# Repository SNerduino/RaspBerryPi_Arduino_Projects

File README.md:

# RaspBerryPi_Arduino_Projects
These are my personal tutorials and projects for raspberry pi and (or) arduino.

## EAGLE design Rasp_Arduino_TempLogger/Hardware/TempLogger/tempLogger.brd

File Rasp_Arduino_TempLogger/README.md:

# Temperature plotterThis  project uses a raspberry pi and one or manu arduinos.Each arduino card is connected to a NRF24L01+ RF module that is used for bluetooth low energy communication tool.It also has a humidity-temperature sensor DHT11The raspberry logs the received data and shows it as a graph.For future releases, the raspberry logs are going to be stored in a MySQL database thet can be accessed through A Web app.## Arduino appThe arduino application dépends on the following libraries :DHT Library for communicating with the DHT11 sensorBTLE Library for using NRF24L01+ as A Bluetooth Low Energy advertiserRF24 Library needed for BTLE Library

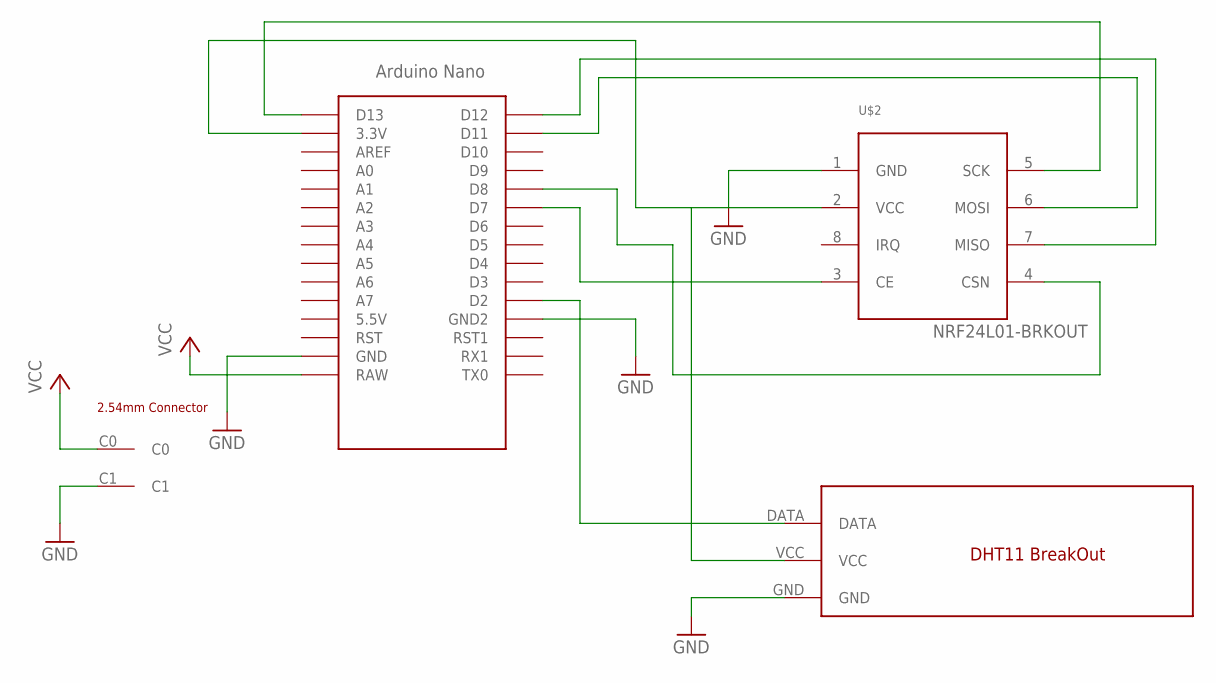
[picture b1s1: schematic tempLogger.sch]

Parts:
U$1: NANO
U$2: NRF24L01-BRKOUT; NRF24L01-BKKOUT
U$3: DHT11BREAKOUTVERTICAL; DHT11BREAKOUT_VERTICAL
U$4: TWO_PINS_CONNECTOR_2_54MM

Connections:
GND: U$1.GND, U$1.GND1 (GND2), U$2.1 (GND), U$3.GND, U$4.C1
unnamed: U$1.3.3V, U$2.2 (VCC), U$3.VCC
unnamed: U$1.D13, U$2.5 (SCK)
unnamed: U$1.D12, U$2.7 (MISO)
unnamed: U$1.D11, U$2.6 (MOSI)
unnamed: U$1.D7, U$2.3 (CE)
unnamed: U$1.D8, U$2.4 (CSN)
unnamed: U$1.D2, U$3.DATA
VCC: U$1.RAW, U$4.C0

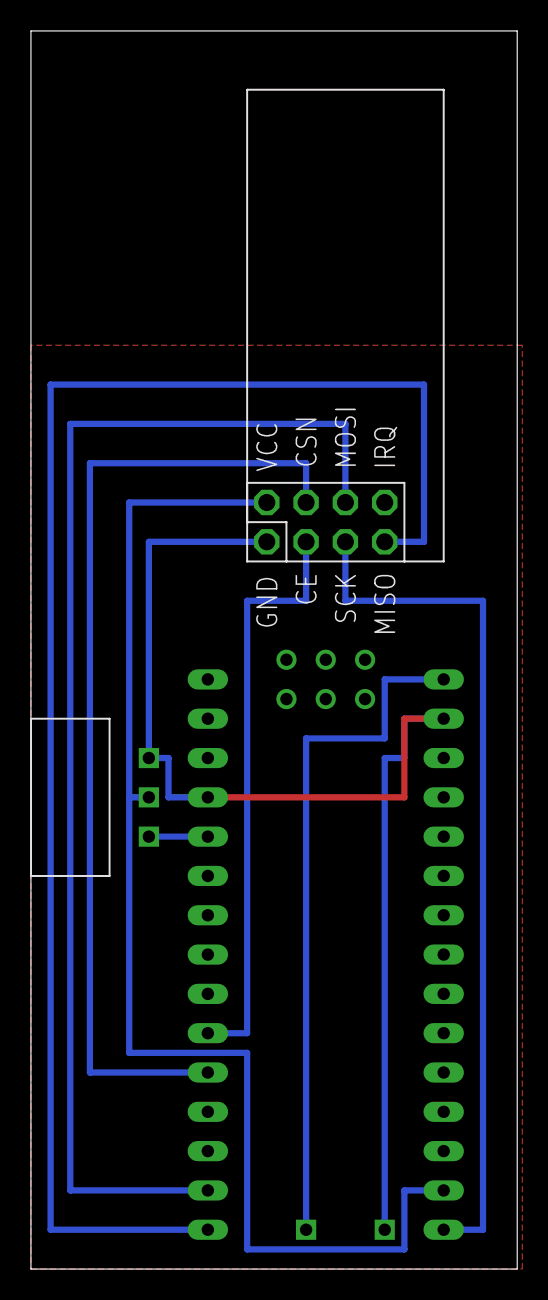
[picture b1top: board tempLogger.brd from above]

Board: 2 copper layers, 31.4 x 80.0 mm, 4 parts (0 on the bottom side), 9 nets.

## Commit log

2017-11-01 Added first Application The Logger
2017-11-01 Added Arduino setup for NRF24L01+ on arduino uno
2017-11-01 Added Rpi connections for the NRF24L01+
2017-11-01 Added arduino templogger code
2017-11-01 Logger now displays the temperature in degrees
2017-11-05 Added MySQL database logging
2017-11-05 Added humidity to the advertised data
2017-11-05 Added Database capability to the logger
2017-11-05 Added a webpage to view the temperature and humidity evolution through time
2017-11-07 Added new data fetching php files
2017-11-09 Created hardware eagle files
